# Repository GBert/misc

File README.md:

OpenWrt railroad files
======================

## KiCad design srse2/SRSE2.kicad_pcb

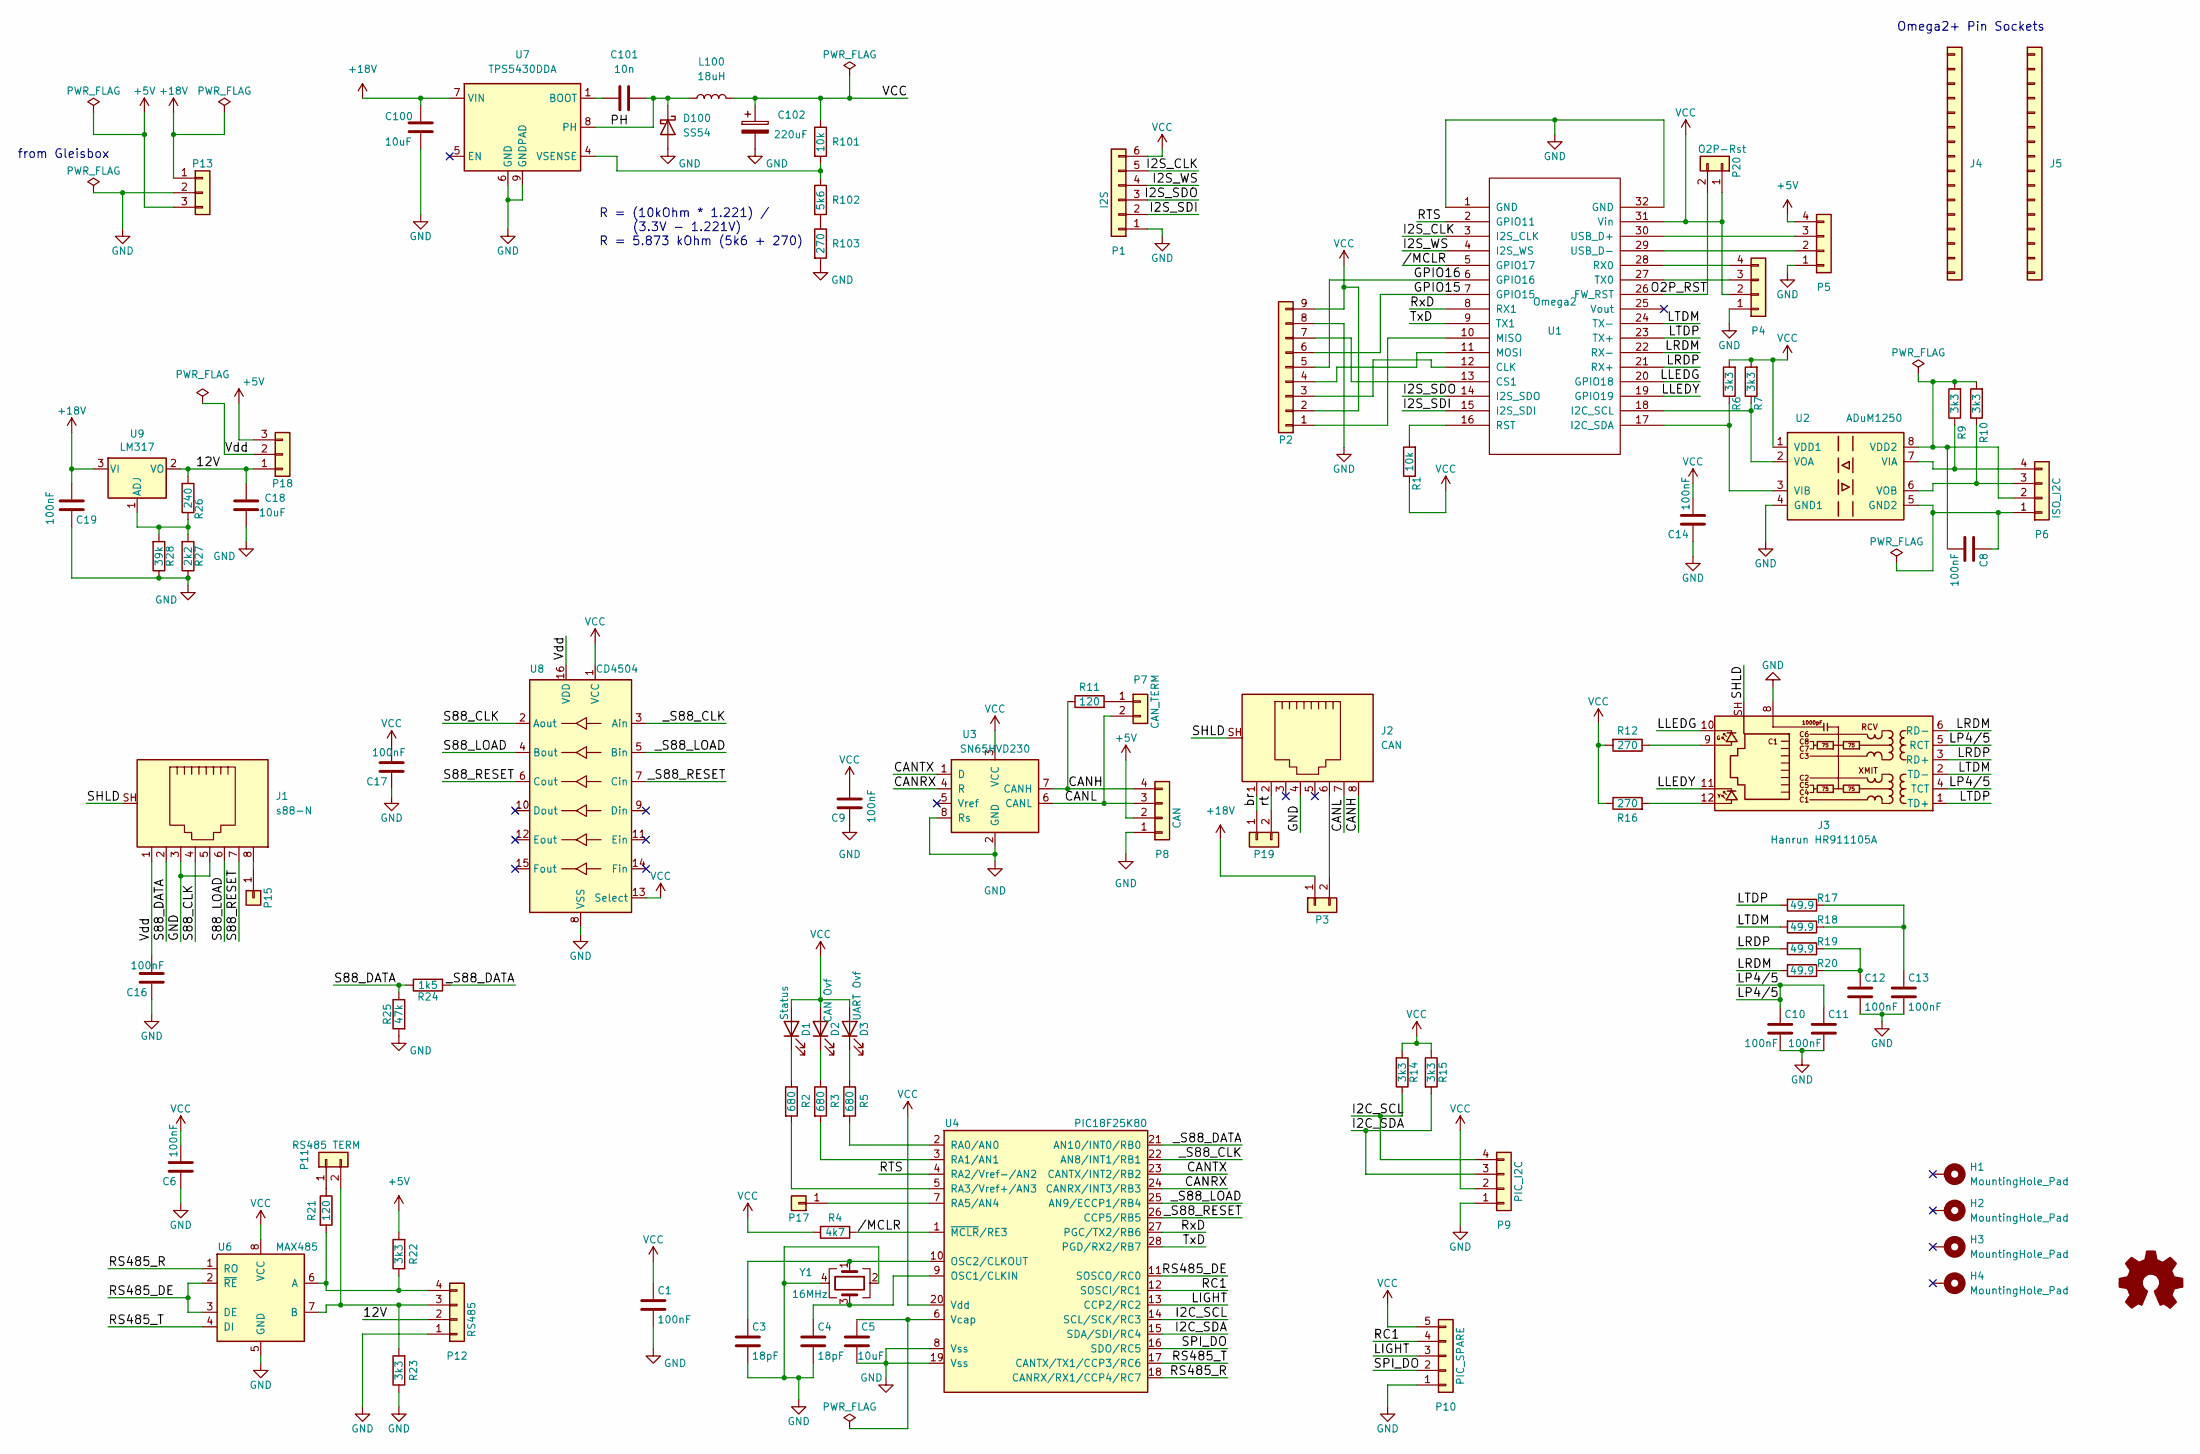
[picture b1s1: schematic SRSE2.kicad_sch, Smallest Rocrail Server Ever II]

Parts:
C1, C6, C8, C9, C10, C11, C12, C13, C14, C16, C17, C19: 100nF; C_0805_2012Metric_Pad1.18x1.45mm_HandSolder; LCSC C49678
C3, C4: 18pF; C_0603_1608Metric; LCSC C1647
C5, C18, C100: 10uF; C_1206_3216Metric_Pad1.33x1.80mm_HandSolder; LCSC C13585
C101: 10n; C_0603_1608Metric_Pad1.08x0.95mm_HandSolder; LCSC C57112
C102: 220uF; CP_EIA-7343-31_Kemet-D_Pad2.25x2.55mm_HandSolder; LCSC C116743
D1: Status; LED_D3.0mm
D2: CAN Ovf; LED_D3.0mm
D3: UART Ovf; LED_D3.0mm
D100: SS54; D_SMA; LCSC C22452
H1, H2, H3, H4: MountingHole_Pad; MountingHole_3mm
J1: s88-N; MEBP_8-8G
J2: CAN; MEBP_8-8G_1
J3: Hanrun HR911105A; RJ45_Hanrun_HR911105A_Horizontal
J4, J5: Conn16; LCSC C2938437
L100: 18uH; L_10.4x10.4_H4.8; LCSC C225049
P1: I2S; PinHeader_1x06_P2.54mm_Vertical
P2: CONN_01X09; PinHeader_1x09_P2.54mm_Vertical
P3, P19: CONN_01X02; PinHeader_1x02_P2.54mm_Vertical
P4: CONN_01X04; JST_PH_B4B-PH-K_1x04_P2.00mm_Vertical
P5: CONN_01X04; PinHeader_1x04_P2.54mm_Vertical
P6: ISO_I2C; JST_PH_B4B-PH-K_1x04_P2.00mm_Vertical
P7: CAN_TERM; PinHeader_1x02_P2.54mm_Vertical
P8: CAN; JST_PH_B4B-PH-K_1x04_P2.00mm_Vertical
P9: PIC_I2C; JST_PH_B4B-PH-K_1x04_P2.00mm_Vertical
P10: PIC_SPARE; PinHeader_1x05_P2.54mm_Vertical
P11: RS485 TERM; PinHeader_1x02_P2.54mm_Vertical
P12: RS485; JST_PH_B4B-PH-K_1x04_P2.00mm_Vertical
P13, P18: CONN_01X03; PinHeader_1x03_P2.54mm_Vertical
P15, P17: RA5; PinHeader_1x01_P2.54mm_Vertical
P20: O2P-Rst; PinHeader_1x02_P2.54mm_Vertical
R1: 10k; R_0805_2012Metric_Pad1.20x1.40mm_HandSolder; LCSC C17414
R2, R3, R5: 680; R_0805_2012Metric_Pad1.20x1.40mm_HandSolder; LCSC C17798
R4: 4k7; R_0805_2012Metric_Pad1.20x1.40mm_HandSolder; LCSC C17673
R6, R7, R9, R10, R14, R15, R22, R23: 3k3; R_0805_2012Metric_Pad1.20x1.40mm_HandSolder; LCSC C26010
R11, R21: 120; R_1206_3216Metric_Pad1.30x1.75mm_HandSolder; LCSC C17909
R12, R16, R103: 270; R_0603_1608Metric_Pad0.98x0.95mm_HandSolder; LCSC C22966
R17, R18, R19, R20: 49.9; R_0805_2012Metric_Pad1.20x1.40mm_HandSolder; LCSC C17720
R24: 1k5; R_0805_2012Metric_Pad1.20x1.40mm_HandSolder; LCSC C4310
R25: 47k; R_0805_2012Metric_Pad1.20x1.40mm_HandSolder; LCSC C17713
R26: 240; R_0603_1608Metric_Pad0.98x0.95mm_HandSolder; LCSC C23350
R27: 2k2; R_0603_1608Metric_Pad0.98x0.95mm_HandSolder; LCSC C4190
R28: 39k; R_0603_1608Metric_Pad0.98x0.95mm_HandSolder; LCSC C23153
R101: 10k; R_0603_1608Metric_Pad0.98x0.95mm_HandSolder; LCSC C25804
R102: 5k6; R_0603_1608Metric_Pad0.98x0.95mm_HandSolder; LCSC C23189
SYM1: Logo_Open_Hardware_Small; CC_Logo
U1: Omega2
U2: ADuM1250; SOIC-8_3.9x4.9mm_P1.27mm
U3: SN65HVD230; SOIC-8_3.9x4.9mm_P1.27mm; LCSC C12084
U4: PIC18F25K80; SSOP-28_5.3x10.2mm_P0.65mm; LCSC C26838
U6: MAX485; SOIC-8_3.9x4.9mm_P1.27mm
U7: TPS5430DDA; TI_SO-PowerPAD-8_ThermalVias; LCSC C9864
U8: CD4504; SOIC-16_3.9x9.9mm_P1.27mm; LCSC C151885
U9: LM317; TO-252-2; LCSC C75510
Y1: 16MHz; Crystal_SMD_3225-4Pin_3.2x2.5mm; LCSC C13738

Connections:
+5V: P5.4, P8.2, P13.3, P18.3, R22.2
+18V: C19.2, C100.2, P3.1, P13.1, U7.7 (VIN), U9.3 (VI)
/12V: C18.1, P12.2, P18.1, R26.2, U9.2 (VO)
/CANH: J2.8, P8.4, R11.1, U3.7 (CANH)
/CANL: J2.7, P7.2, P8.3, U3.6 (CANL)
/CANRX: U3.4 (R), U4.24 (CANRX/INT3/RB3)
/CANTX: U3.1 (D), U4.23 (CANTX/INT2/RB2)
/GPIO15: P2.6, U1.7 (GPIO15)
/GPIO16: P2.5, U1.6 (GPIO16)
/I2C_SCL: P9.4, R14.1, U4.14 (SCL/SCK/RC3)
/I2C_SDA: P9.3, R15.2, U4.15 (SDA/SDI/RC4)
/I2S_CLK: P1.5, U1.3 (I2S_CLK)
/I2S_SDI: P1.2, U1.15 (I2S_SDI)
/I2S_SDO: P1.3, U1.14 (I2S_SDO)
/I2S_WS: P1.4, U1.4 (I2S_WS)
/LIGHT: P10.3, U4.13 (CCP2/RC2)
/LLEDG: J3.10, U1.20 (GPIO18)
/LLEDY: J3.11, U1.19 (GPIO19)
/LP4/5: C10.1, C11.1, J3.4 (TCT), J3.5 (RCT)
/LRDM: J3.6 (RD-), R20.2, U1.22 (RX-)
/LRDP: J3.3 (RD+), R19.2, U1.21 (RX+)
/LTDM: J3.2 (TD-), R18.2, U1.24 (TX-)
/LTDP: J3.1 (TD+), R17.2, U1.23 (TX+)
/O2P_RST: P20.2, U1.26 (FW_RST)
/PH: C101.2, D100.1 (K), L100.1, U7.8 (PH)
/RC1: P10.4, U4.12 (SOSCI/RC1)
/RS485_DE: U4.11 (SOSCO/RC0), U6.2 (~RE), U6.3 (DE)
/RS485_R: U4.18 (CANRX/RX1/CCP4/RC7), U6.1 (RO)
/RS485_T: U4.17 (CANTX/TX1/CCP3/RC6), U6.4 (DI)
/RTS: U1.2 (GPIO11), U4.4 (RA2/Vref-/AN2)
/RxD: U1.8 (RX1), U4.27 (PGC/TX2/RB6)
/S88_CLK: J1.4, U8.2 (Aout)
/S88_DATA: J1.2, R24.1, R25.1
/S88_LOAD: J1.6, U8.4 (Bout)
/S88_RESET: J1.7, U8.6 (Cout)
/SHLD: J1.SH, J2.SH, J3.SH
/SPI_DO: P10.2, U4.16 (SDO/RC5)
/TxD: U1.9 (TX1), U4.28 (PGD/RX2/RB7)
/Vdd: C16.2, J1.1, P18.2, U8.16 (VDD)
/_S88_CLK: U4.22 (AN8/INT1/RB1), U8.3 (Ain)
/_S88_DATA: R24.2, U4.21 (AN10/INT0/RB0)
/_S88_LOAD: U4.25 (AN9/ECCP1/RB4), U8.5 (Bin)
/_S88_RESET: U4.26 (CCP5/RB5), U8.7 (Cin)
/br: J2.1, P19.1
/rt: J2.2, P19.2
//MCLR: R4.1, U1.5 (GPIO17), U4.1 (~MCLR/RE3)
GND: C1.2, C3.2, C4.2, C5.2, C6.1, C9.1, C10.2, C11.2, C12.2, C13.2, C14.1, C16.1, C17.1, C18.2, C19.1, C100.1, C102.2, D100.2 (A), J1.3, J1.5, J2.4, J3.8, P1.1, P2.8, P4.1, P5.1, P8.1, P9.1, P10.1, P12.1, P13.2, R23.1, R25.2, R27.1, R28.1, R103.2, U1.1 (GND), U1.32 (GND), U2.4 (GND1), U3.2 (GND), U3.8 (Rs), U4.8 (Vss), U4.19 (Vss), U6.5 (GND), U7.6 (GND), U7.9 (GNDPAD), U8.8 (VSS), Y1.2, Y1.4
unnamed: C12.1, R19.1, R20.1
unnamed: C13.1, R17.1, R18.1
unnamed: D1.1 (K), R2.1
unnamed: D2.1 (K), R3.1
unnamed: D3.1 (K), R5.1
unnamed: J3.9, R12.1
unnamed: J3.12, R16.2
unnamed: P2.1, U1.10 (MISO)
unnamed: P2.3, U1.12 (CLK)
unnamed: P2.4, U1.11 (MOSI)
unnamed: P2.7, U1.13 (CS1)
unnamed: J2.6, P3.2
unnamed: P4.3, U1.27 (TX0)
unnamed: P4.4, U1.28 (RX0)
unnamed: P5.2, U1.29 (USB_D-)
unnamed: P5.3, U1.30 (USB_D+)
unnamed: C8.1, P6.1, U2.5 (GND2)
unnamed: C8.2, P6.2, R9.2, R10.2, U2.8 (VDD2)
unnamed: P6.3, R10.1, U2.6 (VOB)
unnamed: P6.4, R9.1, U2.7 (VIA)
unnamed: P7.1, R11.2
unnamed: P11.1, R21.1
unnamed: P11.2, P12.3, R23.2, U6.7 (B)
unnamed: P12.4, R21.2, R22.1, U6.6 (A)
unnamed: J1.8, P15.1
unnamed: P17.1, U4.7 (RA5/AN4)
unnamed: R102.2, R103.1
unnamed: R7.1, U1.18 (I2C_SCL), U2.2 (VOA)
unnamed: R6.1, U1.17 (I2C_SDA), U2.3 (VIB)
unnamed: R1.2, U1.16 (RST)
unnamed: C4.1, U4.9 (OSC1/CLKIN), Y1.3
unnamed: C3.1, U4.10 (OSC2/CLKOUT), Y1.1
unnamed: R5.2, U4.2 (RA0/AN0)
unnamed: R3.2, U4.3 (RA1/AN1)
unnamed: R2.2, U4.5 (RA3/Vref+/AN3)
unnamed: C5.1, U4.6 (Vcap)
unnamed: C101.1, U7.1 (BOOT)
unnamed: R101.2, R102.1, U7.4 (VSENSE)
unnamed: R26.1, R27.2, R28.2, U9.1 (ADJ)
VCC: C1.1, C6.2, C9.2, C14.2, C17.2, C102.1, D1.2 (A), D2.2 (A), D3.2 (A), L100.2, P1.6, P2.2, P2.9, P4.2, P9.2, P10.5, P20.1, R1.1, R4.2, R6.2, R7.2, R12.2, R14.2, R15.1, R16.1, R101.1, U1.31 (Vin), U2.1 (VDD1), U3.3 (VCC), U4.20 (Vdd), U6.8 (VCC), U8.1 (VCC), U8.13 (Select)

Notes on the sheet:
from Gleisbox
R = (10kOhm * 1.221) / (3.3V - 1.221V) R = 5.873 kOhm (5k6 + 270)
Omega2+ Pin Sockets

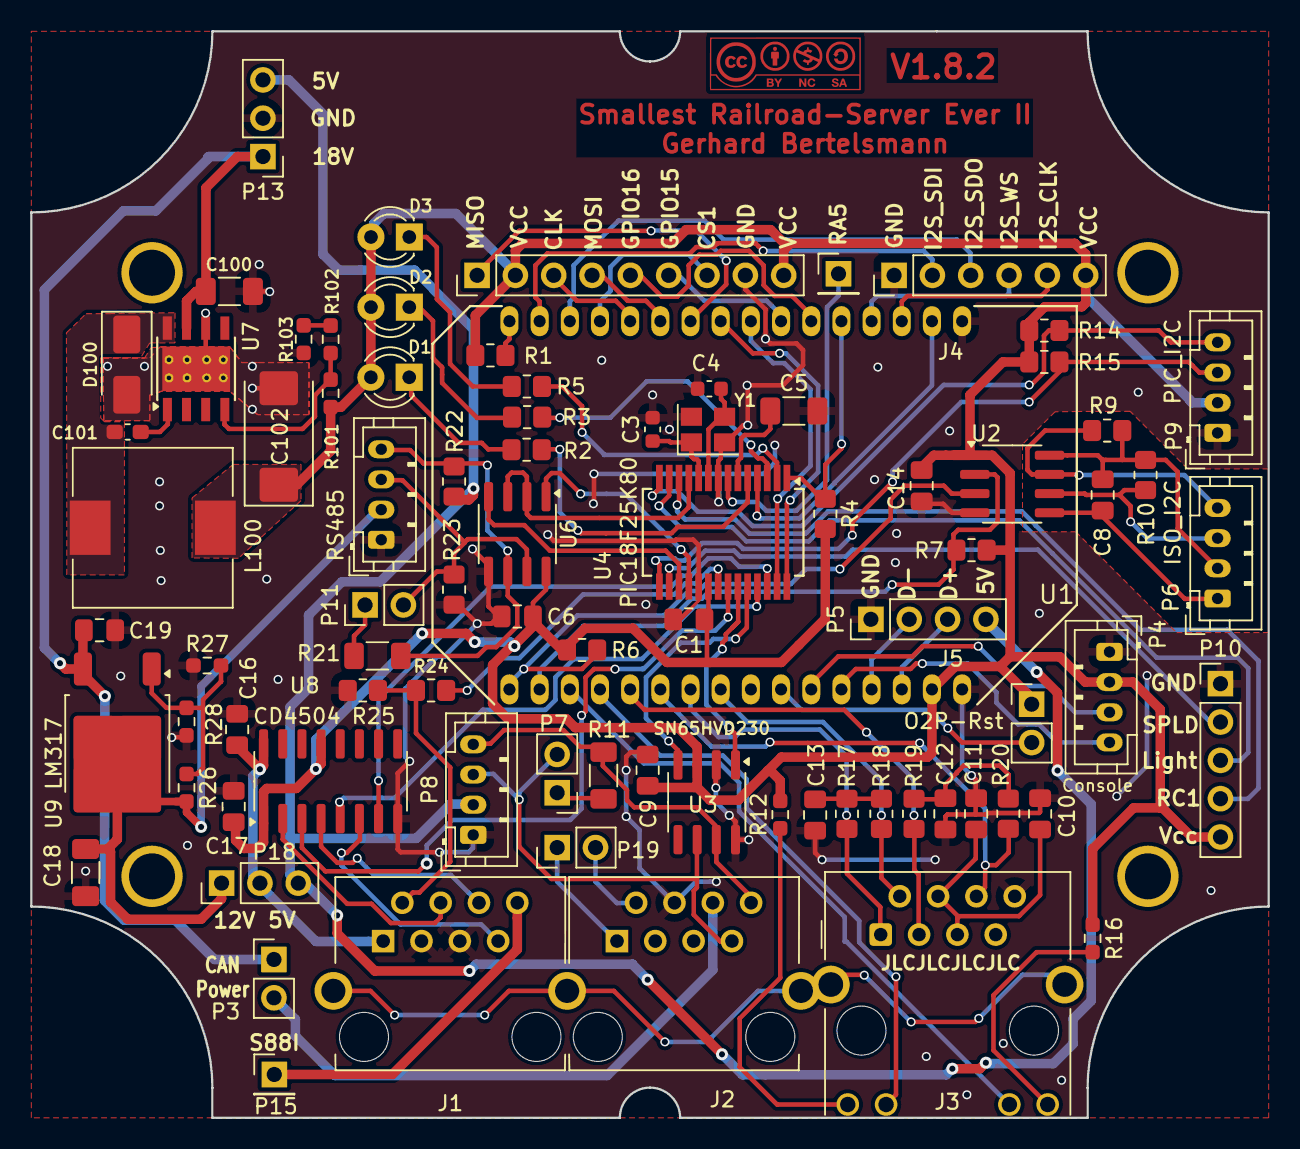
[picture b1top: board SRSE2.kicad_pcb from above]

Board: 2 copper layers, 82.0 x 72.0 mm, 90 parts (0 on the bottom side), 87 nets.

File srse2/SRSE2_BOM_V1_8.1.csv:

Comment,Designator,Footprint,LCSC
"100nF","C1,C6,C8,C9,C10,C11,C12,C13,C14,C16,C17,C19","Capacitors_SMD:C_0805_HandSoldering","C49678"
"10n","C101","Capacitor_SMD:C_0603_1608Metric_Pad1.08x0.95mm_HandSolder","C57112"
"220uF","C102","Capacitor_Tantalum_SMD:CP_EIA-7343-31_Kemet-D_Pad2.25x2.55mm_HandSolder","C116743"
"18pF","C3,C4","Capacitors_SMD:C_0805_HandSoldering","C1797"
"10uF","C5,C18,C100","Capacitor_SMD:C_1206_3216Metric_Pad1.33x1.80mm_HandSolder","C13585"
"SS54","D100","Diode_SMD:D_SMA","C22452"
"15uH","L100","Inductor_SMD:L_10.4x10.4_H4.8","C225048"
"10k","R1","Resistors_SMD:R_0805_HandSolderingII","C17414"
"10k","R101","Resistor_SMD:R_0603_1608Metric_Pad0.98x0.95mm_HandSolder","C25804"
"5k6","R102","Resistor_SMD:R_0603_1608Metric_Pad0.98x0.95mm_HandSolder","C23189"
"270","R103","Resistor_SMD:R_0603_1608Metric_Pad0.98x0.95mm_HandSolder","C22966"
"120","R11,R21","Resistors_SMD:R_1206_HandSolderingII","C17909"
"270","R12,R16","Resistors_SMD:R_0805_HandSolderingII","C17590"
"49.9","R17,R18,R19,R20","Resistors_SMD:R_0805_HandSolderingII","C17720"
"680","R2,R3,R5","Resistors_SMD:R_0805_HandSolderingII","C17798"
"1k5","R24","Resistors_SMD:R_0805_HandSolderingII","C4310"
"47k","R25","Resistors_SMD:R_0805_HandSolderingII","C17713"
"240","R26","Resistors_SMD:R_0805_HandSolderingII","C17572"
"2k2","R27","Resistors_SMD:R_0805_HandSolderingII","C17520"
"39k","R28","Resistors_SMD:R_0805_HandSolderingII","C25826"
"4k7","R4","Resistors_SMD:R_0805_HandSolderingII","C17673"
"3k3","R6,R7,R9,R10,R14,R15,R22,R23","Resistors_SMD:R_0805_HandSolderingII","C26010"
"SN65HVD230","U3","Package_SO:SOIC-8_3.9x4.9mm_P1.27mm","C12084"
"PIC18F25K80","U4","w_smd_dil:ssop-28","C26838"
"TPS5430DDA","U7","Package_SO:TI_SO-PowerPAD-8_ThermalVias","C9864"
"CD4504","U8","Package_SO:SO-16_3.9x9.9mm_P1.27mm","C151885"
"LM317","U9","Package_TO_SOT_SMD:TO-252-2","C75510"
"16MHz","Y1","Crystal:Crystal_SMD_3225-4Pin_3.2x2.5mm","C13738"

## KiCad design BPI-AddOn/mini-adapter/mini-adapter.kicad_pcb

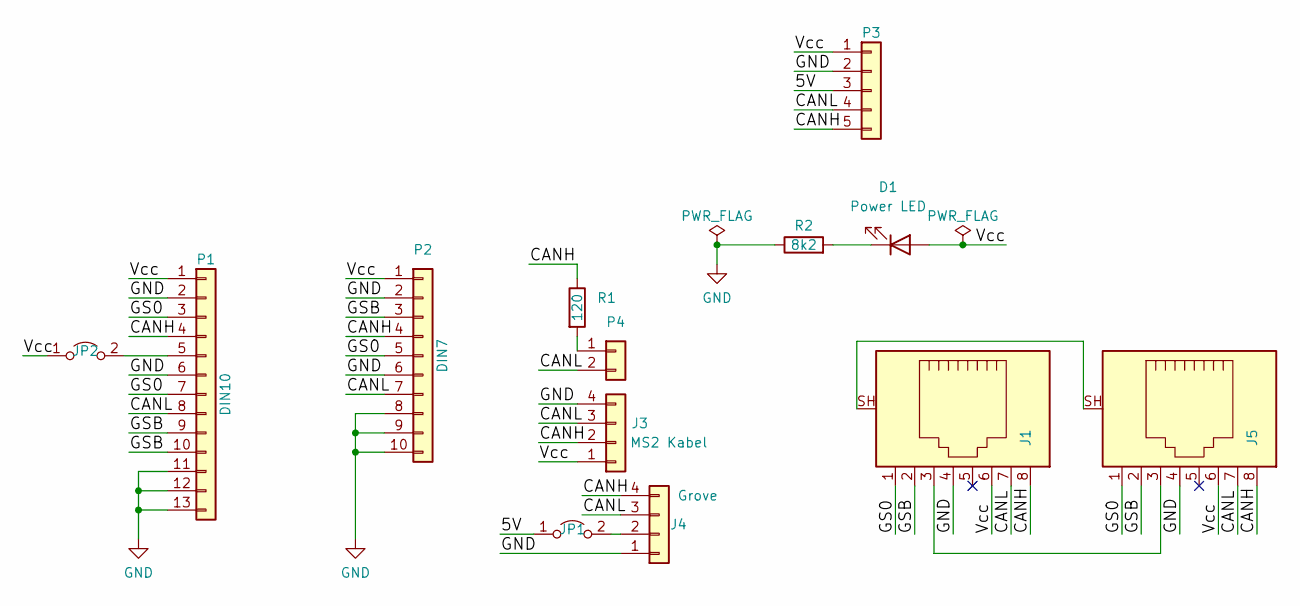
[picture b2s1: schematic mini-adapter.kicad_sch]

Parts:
D1: Power LED; LED_D3.0mm
J1, J5: RJ45; megbp8
J3: MS2 Kabel; B4B-ZR_LF_SN
J4: Grove; JST_PH_B4B-PH-K_1x04_P2.00mm_Vertical
JP1: 5V; PinHeader_1x02_P2.54mm_Vertical
JP2: MS1 Master; PinHeader_1x02_P2.54mm_Vertical
P1: DIN10; minidin-10
P2: DIN7; minidin-7
P3: CONN_01X05; PinHeader_1x05_P2.54mm_Vertical
P4: CAN Term; PinHeader_1x02_P2.54mm_Vertical
R1: 120; R_Axial_DIN0204_L3.6mm_D1.6mm_P7.62mm_Horizontal
R2: 8k2; R_Axial_DIN0204_L3.6mm_D1.6mm_P7.62mm_Horizontal

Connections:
/5V: JP1.1 (A), P3.3
/CANH: J1.8, J3.2, J4.4, J5.8, P1.4, P2.4, P3.5, R1.1
/CANL: J1.7, J3.3, J4.3, J5.7, P1.8, P2.7, P3.4, P4.2
/GS0: J1.1, J5.1, P1.3, P1.7, P2.5
/GSB: J1.2, J5.2, P1.9, P1.10, P2.3
/Vcc: D1.2 (A), J1.6, J3.1, J5.6, JP2.1 (A), P1.1, P2.1, P3.1
GND: J1.4, J3.4, J4.1, J5.4, P1.2, P1.6, P1.11, P1.12, P1.13, P2.2, P2.6, P2.8, P2.9, P2.10, P3.2, R2.1
unnamed: D1.1 (K), R2.2
unnamed: J1.3, J5.3
unnamed: J1.SH, J5.SH
unnamed: J4.2, JP1.2 (B)
unnamed: JP2.2 (B), P1.5
unnamed: P4.1, R1.2

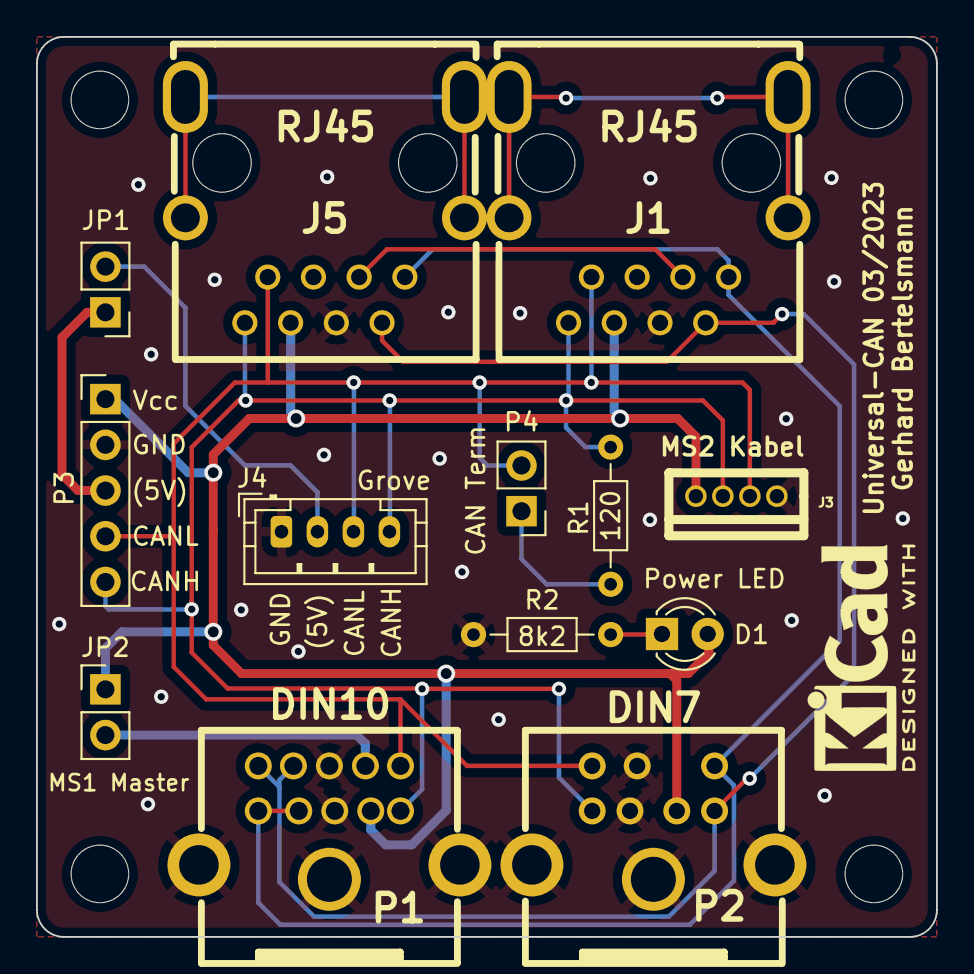
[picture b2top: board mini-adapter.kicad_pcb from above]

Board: 2 copper layers, 50.0 x 50.0 mm, 13 parts (0 on the bottom side), 13 nets.

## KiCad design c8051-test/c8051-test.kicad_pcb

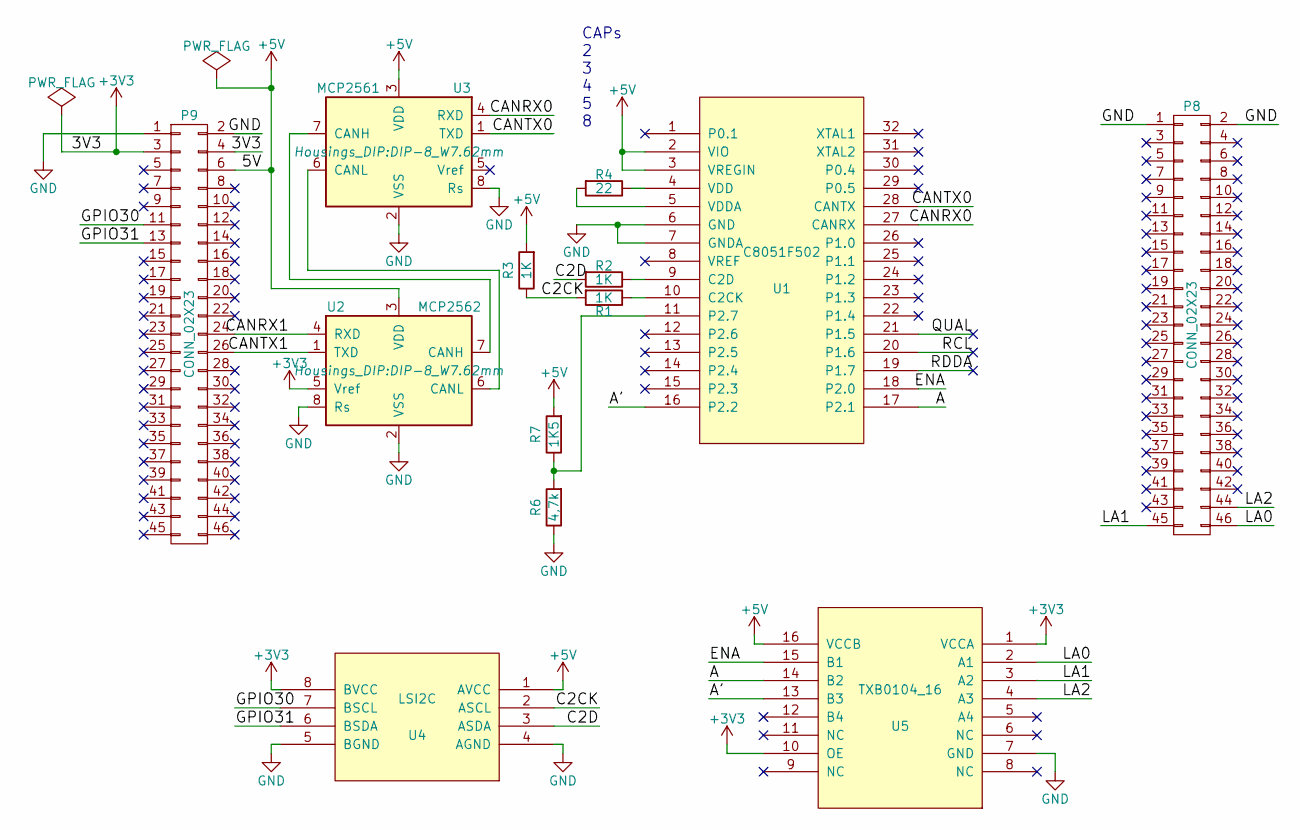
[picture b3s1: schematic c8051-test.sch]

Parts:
P8, P9: CONN_02X23; Pin_Header_Straight_2x23
R1, R2, R3: 1K; R_0805
R4: 22; R_0805
R6: 4,7k; R_0805
R7: 1K5; R_0805
U1: C8051F502; DIP-32_W15.24mm
U2: MCP2562; DIP-8_W7.62mm
U3: MCP2561; DIP-8_W7.62mm
U4: LSI2C; DIP-8_W_ELL
U5: TXB0104_16; DIP-16_W_ELL

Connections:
+3V3: P9.3, P9.4, U2.5 (Vref), U4.8 (BVCC), U5.1 (VCCA), U5.10 (OE)
+5V: P9.6, R3.2, R7.2, U1.2 (VIO), U1.3 (VREGIN), U2.3 (VDD), U3.3 (VDD), U4.1 (AVCC), U5.16 (VCCB)
/A: U1.17 (P2.1), U5.14 (B2)
/A': U1.16 (P2.2), U5.13 (B3)
/C2CK: R1.2, R3.1, U4.2 (ASCL)
/C2D: R2.2, U4.3 (ASDA)
/CANRX0: U1.27 (CANRX), U3.4 (RXD)
/CANRX1: P9.24, U2.4 (RXD)
/CANTX0: U1.28 (CANTX), U3.1 (TXD)
/CANTX1: P9.26, U2.1 (TXD)
/ENA: U1.18 (P2.0), U5.15 (B1)
/GPIO30: P9.11, U4.7 (BSCL)
/GPIO31: P9.13, U4.6 (BSDA)
/LA0: P8.46, U5.2 (A1)
/LA1: P8.45, U5.3 (A2)
/LA2: P8.44, U5.4 (A3)
/QUAL: U1.21 (P1.5)
/RCL: U1.20 (P1.6)
/RDDA: U1.19 (P1.7)
GND: P8.1, P8.2, P9.1, P9.2, R6.1, U1.6 (GND), U1.7 (GNDA), U2.2 (VSS), U2.8 (Rs), U3.2 (VSS), U3.8 (Rs), U4.4 (AGND), U4.5 (BGND), U5.7 (GND)
unnamed: R1.1, U1.10 (C2CK)
unnamed: R2.1, U1.9 (C2D)
unnamed: R4.1, U1.4 (VDD)
unnamed: R4.2, U1.5 (VDDA)
unnamed: R6.2, R7.1, U1.11 (P2.7)
unnamed: U2.6 (CANL), U3.6 (CANL)
unnamed: U2.7 (CANH), U3.7 (CANH)

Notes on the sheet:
CAPs 2 3 4 5 8

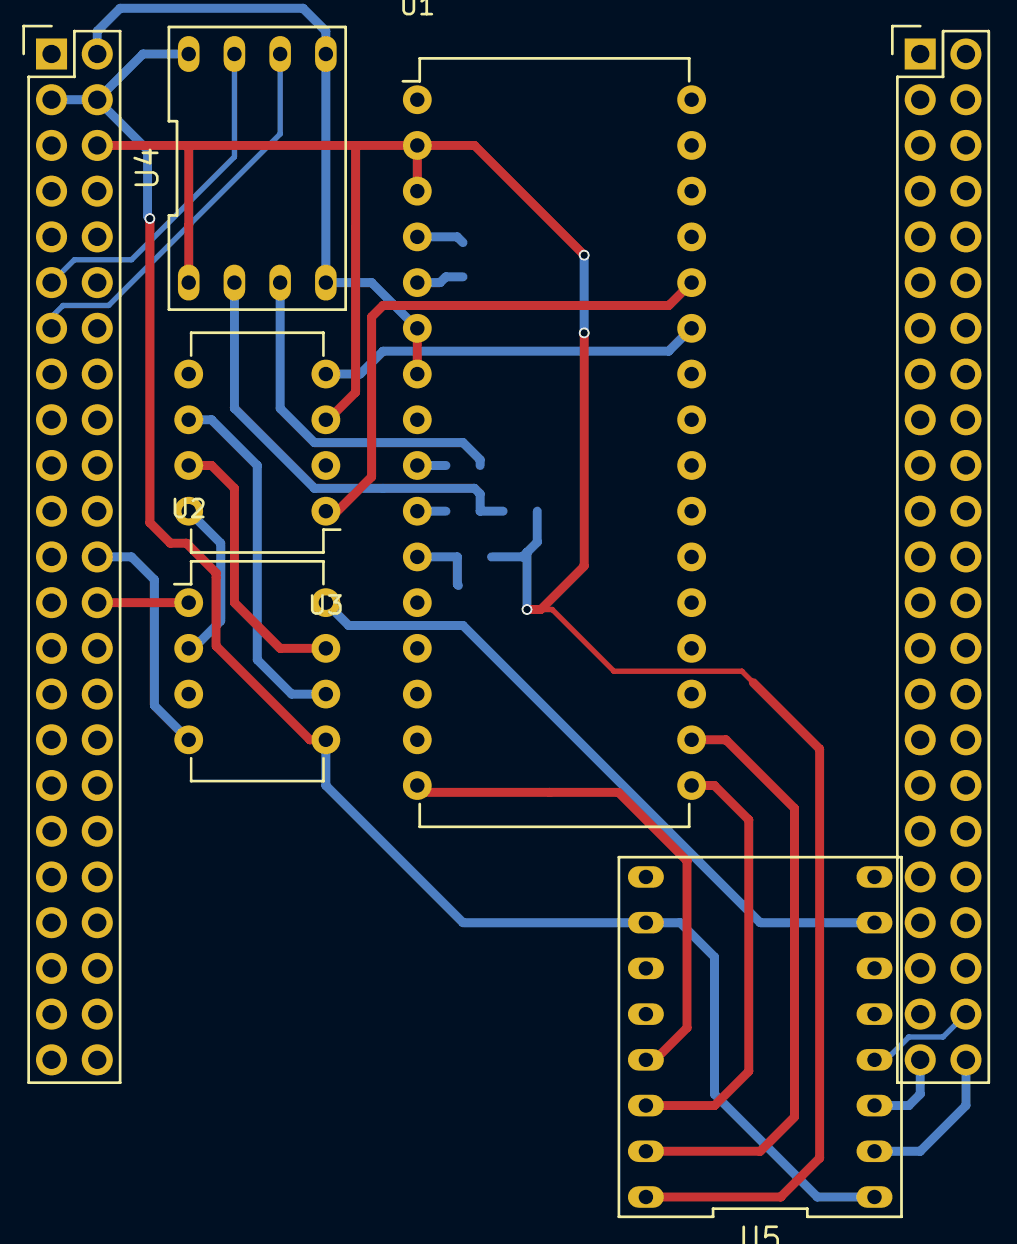
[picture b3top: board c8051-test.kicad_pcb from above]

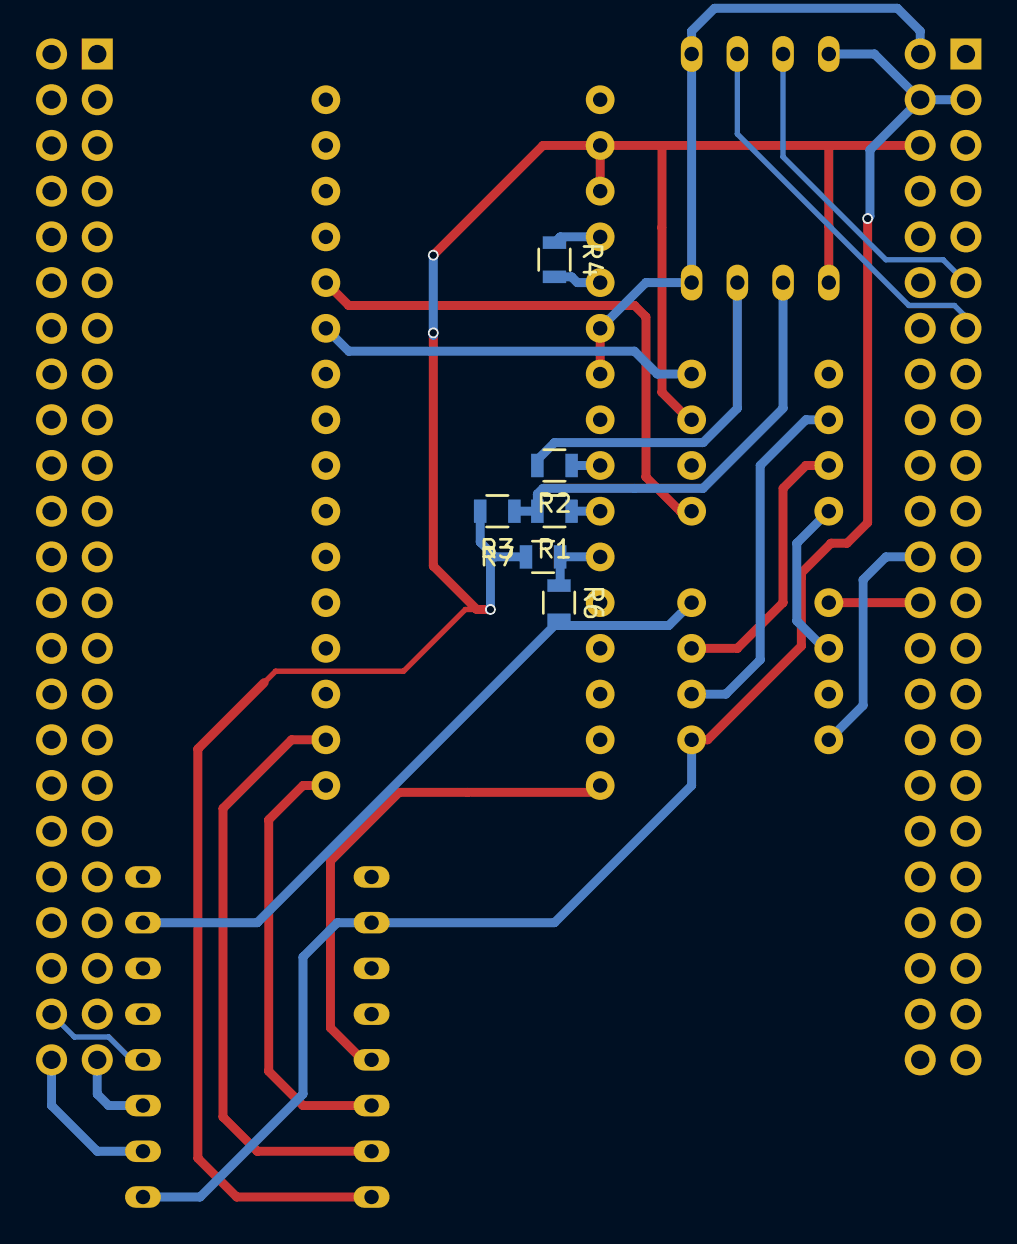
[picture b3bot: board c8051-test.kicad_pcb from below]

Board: 2 copper layers, 13 parts (6 on the bottom side), 24 nets.

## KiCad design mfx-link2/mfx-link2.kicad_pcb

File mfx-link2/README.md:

mfx-Booster/Link - SMD Version
==============================

Booster incl. mfx-R&uuml;kmeldung zusammen mit einem IBT-2 Modul / SMD Version

Kombination aus [mfx-R&uuml;ckmelder](http://www.persmodelrailroad.net/mfx_boost.html) und [DCC Booster](http://www.trainelectronics.com/DCC_Arduino/DCC_Booster), der auch MM und mfx kann

Der mfx-Booster/Link bietet zusammen mit dem IBT-2 Modul und einem entsprechenden Netzteil eine kosteng&uuml;nstige Erweiterung f&uuml;r eine leistungsstarke Zentrale (8A).

Bauteile
--------

Geeignete &Uuml;bertrager:
```
Murata 53040C
Pulse Electronics PA1005.040QNL
```

BOM
---

|Part|Value|Footprint|LCSC Part Number|
|----|-----|---------|----------------|
|C1,C2,C3,C6|100nF|0805|C49678|
|C4,C5|10uf Elko|SMD||
|C7|1nF|0805|C46653|
|D1,D2,D3,D4,D5|US1M|SMA|C412437|
|D6,D7,D8|1N4148WS|SOD-323F|C2128|
|D9|B5819W or BAT43|SOD-123|C8598|
|D10|LED red|LED 0805|C84256|
|D13|LED white|LED 0805|C34499|
|Q1|MMBT5551 or BC817|SOT-23|C2145|
|R0,R1|820 Ohm|0805|C17837|
|R2|390 Ohm|0805|C17655|
|R3|22 Ohm|0805|C17561|
|R4,R6,R16,R19|4k7 Ohm|0805|C17673|
|R5|82 Ohm|0805|C17841|
|R7|1k Ohm|0805|C17513|
|R8,R9,R10,R11,R12,R13,R14|1k Ohm|1206|C4410|
|R15|1k5 Ohm|0805|C4310|
|R17,R22|10k Ohm|0805|C17414|
|R18|560 Ohm|0805|C28636|
|R20,R21|3k3 Ohm|0805|C26010|
|R23|1k8 Ohm|0805|C17398|
|SW1|Micro Taster|||
|T1|Murata 53040C|||
|U1|6N137|DIL8||
|U2|7805|TO-252-2 DPAK|C58069|
|U3|LM393|SOIC-8|C7955|
|U4|78L05|SOT-89-3|C71137|
|U5|PIC16F1709|SO-20||
|P1|AKL-101-04|4pin RM5.08||
|P1|AKL-059-02|2pin RM3.5||
|P4,P5|Grove Socket|GRV CONNEC4PIN||

JLCPB SMT Assembly
------------------

|Art      | Datei |
|---------|-------|
|PCB      |gerber/mfx-link2_072021.ZIP|
|BOM      |mfx-link2.csv|
|CPL      |gerber/mfx-link2-top-pos.csv|

Reichelt Listen
---------------

SMD Teile (entspricht JLCPCB Bestückung)
[mfx-booster-link2-smd](https://www.reichelt.de/my/1850634)

Rest (ohne IBT-2 und ohne LCD)
[mfx-booster-link2](https://www.reichelt.de/my/1850613)

IBT-Mod
-------

Beschaltung
-----------

Changelog
---------
| Version | Anmerkung |
|---------|-----------|
|062017   |erste Version|
|052021   |überarbeitete Version für SMT Fertigung bei JLCPCB|
|062021   |R17 gegen Masse nicht gegen VCC|
|         |C7 1nF Kondensator hinzugefügt|
|         |1N4148 Pads vergrössert|
|         |R18 vergrössert von 270 auf 560 Ohm wegen LED Stärke|
|072021   |Spannungsteilier R22/23 zur Messung der Versorgungsspannung|

Backup
------

The latency for synchronous interrupts is three or four
instruction cycles. For asynchronous interrupts, the
latency is three to five instruction cycles, depending
on when the interrupt occurs.

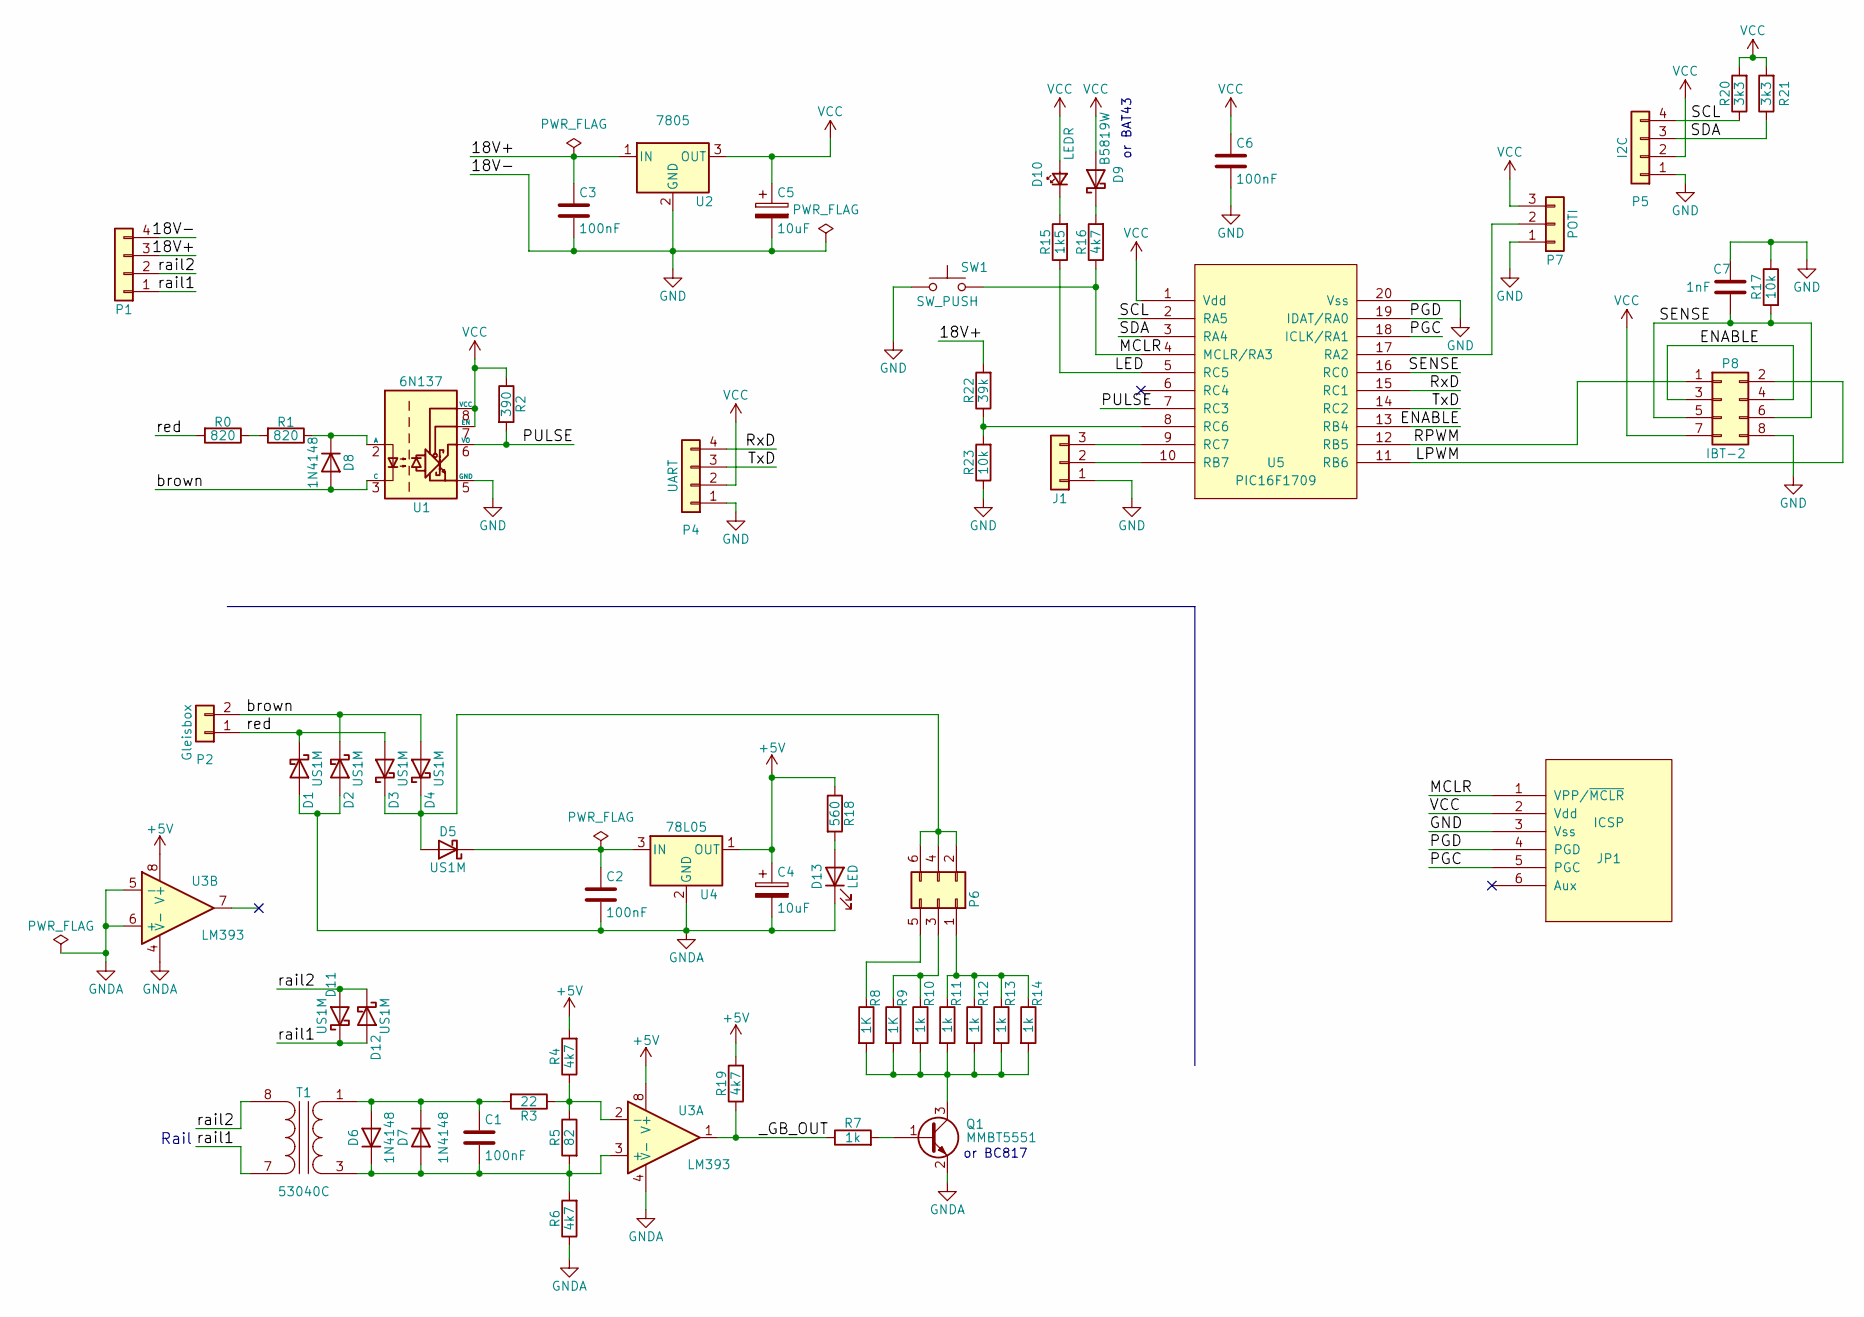
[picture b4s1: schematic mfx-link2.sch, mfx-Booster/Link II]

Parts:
C1, C2, C3, C6: 100nF; C_0805_2012Metric_Pad1.18x1.45mm_HandSolder; LCSC C49678
C4, C5: 10uF; c_elec_5x5.3
C7: 1nF; C_0805_2012Metric_Pad1.18x1.45mm_HandSolder; LCSC C46653
D1, D2, D3, D4, D5, D11, D12: US1M; D_SMA; LCSC C412437
D6, D7, D8: 1N4148; D_SOD-323F; LCSC C2128
D9: B5819W; D_SOD-123; LCSC C8598
D10: LEDR; LED_0805; LCSC C84256
D13: LED; LED_0805; LCSC C34499
J1: Conn_01x03; PinHeader_1x03_P1.27mm_Vertical
JP1: ICSP
P1: Conn_01x04; akl0711,5-4
P2: Gleisbox; pt_1,5-2-3,5-h
P4: UART; b4b-ph-kl
P5: I2C; b4b-ph-kl
P6: CONN_02X03; Pin_Header_Straight_2x03
P7: POTI; Pin_Header_Straight_1x03
P8: IBT-2; Socket_Strip_Straight_2x04
Q1: MMBT5551; SOT-23; LCSC C2145
R0, R1: 820; R_0805_HandSolderingII; LCSC C17837
R2: 390; R_0805_HandSolderingII; LCSC C17655
R3: 22; R_0805_HandSolderingII; LCSC C17561
R4, R6, R16, R19: 4k7; R_0805_HandSolderingII; LCSC C17673
R5: 82; R_0805_HandSolderingII; LCSC C17841
R7: 1k; R_0805_HandSolderingII; LCSC C17513
R8, R9: 1K; R_1206_HandSolderingII; LCSC C4410
R10, R11, R12, R13, R14: 1k; R_1206_HandSolderingII; LCSC C4410
R15: 1k5; R_0805_HandSolderingII; LCSC C4310
R17, R23: 10k; R_0805_HandSolderingII; LCSC C17414
R18: 560; R_0805_HandSolderingII; LCSC C28636
R20, R21: 3k3; R_0805_HandSolderingII; LCSC C26010
R22: 39k; R_0805_HandSolderingII; LCSC C25826
SW1: SW_PUSH; PCB_PUSH
T1: 53040C; 530x0C
U1: 6N137; dil_8-300_socket
U2: 7805; TO-252-2; LCSC C58069
U3: LM393; SOIC-8_3.9x4.9mm_P1.27mm; LCSC C7955
U4: 78L05; SOT-89-3; LCSC C71136
U5: PIC16F1709; MODULE

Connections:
+5V: C4.1, R4.2, R18.1, R19.2, U3.8 (V+), U4.1 (OUT)
/18V+: C3.1, P1.3, R22.2, U2.1 (IN)
/ENABLE: P8.3, P8.4, U5.13 (RB4)
/LED: R15.1, U5.5 (RC5)
/LPWM: P8.2, U5.11 (RB6)
/MCLR: JP1.1 (VPP/~MCLR), R16.1, SW1.2, U5.4 (MCLR/RA3)
/PGC: JP1.5 (PGC), U5.18 (ICLK/RA1)
/PGD: JP1.4 (PGD), U5.19 (IDAT/RA0)
/PULSE: R2.2, U1.6 (VO), U5.7 (RC3)
/RPWM: P8.1, U5.12 (RB5)
/RxD: P4.4, U5.15 (RC1)
/SCL: P5.4, R20.1, U5.2 (RA5)
/SDA: P5.3, R21.1, U5.3 (RA4)
/SENSE: C7.2, P8.5, P8.6, R17.2, U5.16 (RC0)
/TxD: P4.3, U5.14 (RC2)
/_GB_OUT: R7.1, R19.1, U3.1
/brown: D2.1 (K), D4.2 (A), D8.2 (A), P2.2, U1.3 (C)
/rail1: D11.1 (K), D12.2 (A), P1.1, T1.7 (SA)
/rail2: D11.2 (A), D12.1 (K), P1.2, T1.8 (SB)
/red: D1.1 (K), D3.2 (A), P2.1, R0.2
GND: C3.2, C5.2, C6.2, C7.1, J1.1, JP1.3 (Vss), P1.4, P4.1, P5.1, P7.1, P8.8, R17.1, R23.1, SW1.1, U1.5 (GND), U2.2 (GND), U5.20 (Vss)
GNDA: C2.2, C4.2, D1.2 (A), D2.2 (A), D13.1 (K), Q1.2 (E), R6.1, U3.4 (V-), U3.5 (-), U3.6 (+), U4.2 (GND)
unnamed: C1.1, D6.2 (A), D7.1 (K), R3.2, T1.1 (AA)
unnamed: C1.2, D6.1 (K), D7.2 (A), R5.2, R6.2, T1.3 (AB), U3.3 (+)
unnamed: C2.1, D5.1 (K), U4.3 (IN)
unnamed: D3.1 (K), D4.1 (K), D5.2 (A), P6.2, P6.4, P6.6
unnamed: D8.1 (K), R1.1, U1.2 (A)
unnamed: D9.1 (K), R16.2
unnamed: D10.1 (K), R15.2
unnamed: D13.2 (A), R18.2
unnamed: J1.2, U5.10 (RB7)
unnamed: J1.3, U5.9 (RC7)
unnamed: P6.1, R11.1, R12.1, R13.1, R14.1
unnamed: P6.3, R9.1, R10.1
unnamed: P6.5, R8.1
unnamed: P7.2, U5.17 (RA2)
unnamed: Q1.1 (B), R7.2
unnamed: Q1.3 (C), R8.2, R9.2, R10.2, R11.2, R12.2, R13.2, R14.2
unnamed: R0.1, R1.2
unnamed: R3.1, R4.1, R5.1, U3.2 (-)
unnamed: R22.1, R23.2, U5.8 (RC6)
VCC: C5.1, C6.1, D9.2 (A), D10.2 (A), JP1.2 (Vdd), P4.2, P5.2, P7.3, P8.7, R2.1, R20.2, R21.2, U1.7 (EN), U1.8 (VCC), U2.3 (OUT), U5.1 (Vdd)

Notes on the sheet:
Rail
or BAT43
or BC817
